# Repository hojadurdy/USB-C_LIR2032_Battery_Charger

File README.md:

# USB-C LIR2032 Battery Charger

### What is it?
A lithium coin cell battery charger for charging LIR2032 rechargeable batteries. 

### Features:

- Standard 5V USB power input
- USB-C connector
- Separate charging IC for each battery
- Charging Voltage - 4.2V
- Charging Current - 13mA
- Undervoltage lockout
- Automatically cuts off power when the battery is fully charged
- Preconditioning and end-of-charge
- Preconditioning of low voltage batteries
- High accuracy preset output voltage regulation (+/-1.0%)
- Current monitoring
- Reverse discharge protection
- Green LED indicating input power
- Red LED indicating charging

### How to Use:
Slide the coin cell battery in the right way. Power the device with a USB port. The Green Power LED will turn on indicating it is getting power from the USB port. Red Charge LED will keep blinking if the battery is not inserted. When the battery is charging, the Red Charge LED will stay on. The Red LED will turn off to let you know when it is fully charged.

### NOTE:

- Only for use with rechargeable LIR2032 cells!
- Do not try to recharge non-rechargeable Lithium coin cell batteries like CR2032!
- Do not charge unattended
- Do not charge damaged cells
- Do not insert the battery in reverse polarity

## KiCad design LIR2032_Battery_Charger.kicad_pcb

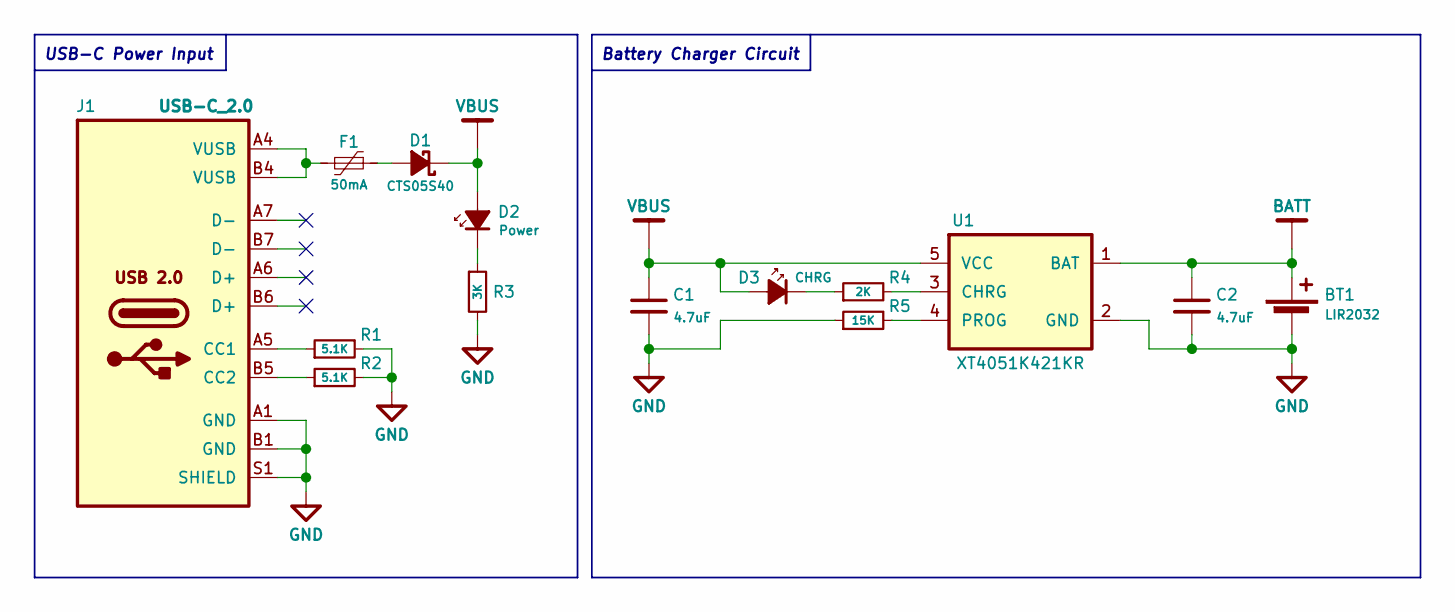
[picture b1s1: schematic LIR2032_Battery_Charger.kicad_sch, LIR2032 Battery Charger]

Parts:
BT1: LIR2032; BatteryHolder_Keystone_1060_1x2032
C1, C2: 4.7uF; C_0402_1005Metric
D1: CTS05S40; CST2
D2: Power; LED_0402_1005Metric
D3: CHRG; LED_0402_1005Metric
F1: 50mA; Fuse_0402_1005Metric
J1: USB-C_2.0; HRO_TYPE-C-31-M-12
R1, R2: 5.1K; R_0402_1005Metric
R3: 3K; R_0402_1005Metric
R4: 2K; R_0402_1005Metric
R5: 15K; R_0402_1005Metric
U1: XT4051K421KR; SOT-553

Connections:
BATT: BT1.1 (+), C2.1, U1.1 (BAT)
GND: BT1.2 (-), C1.2, C2.2, J1.A1 (GND), J1.B1 (GND), J1.S1 (SHIELD), R1.2, R2.2, R3.2, R5.1, U1.2 (GND)
unnamed: D1.2 (A), F1.1
unnamed: D2.1 (K), R3.1
unnamed: F1.2, J1.A4 (VUSB), J1.B4 (VUSB)
unnamed: J1.A5 (CC1), R1.1
unnamed: J1.B5 (CC2), R2.1
unnamed: D3.1 (K), R4.1
unnamed: R4.2, U1.3 (CHRG)
unnamed: R5.2, U1.4 (PROG)
VBUS: C1.1, D1.1 (K), D2.2 (A), D3.2 (A), U1.5 (VCC)

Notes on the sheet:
USB-C Power Input
Battery Charger Circuit

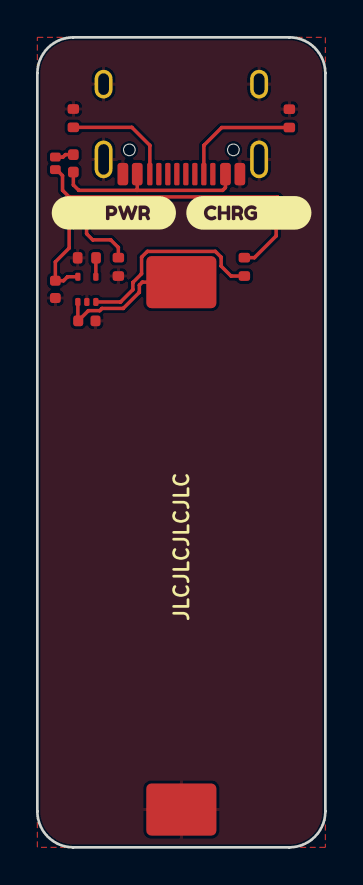
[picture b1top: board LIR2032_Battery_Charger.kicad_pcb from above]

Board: 2 copper layers, 16.0 x 45.0 mm, 16 parts (0 on the bottom side), 11 nets.

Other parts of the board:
kibuzzard-6192C1BF: G***; kibuzzard-6192C1BF
kibuzzard-6192C1F3: G***; kibuzzard-6192C1F3

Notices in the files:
LIR2032_Battery_Charger.kicad_sch:
CC BY-SA 4.0
